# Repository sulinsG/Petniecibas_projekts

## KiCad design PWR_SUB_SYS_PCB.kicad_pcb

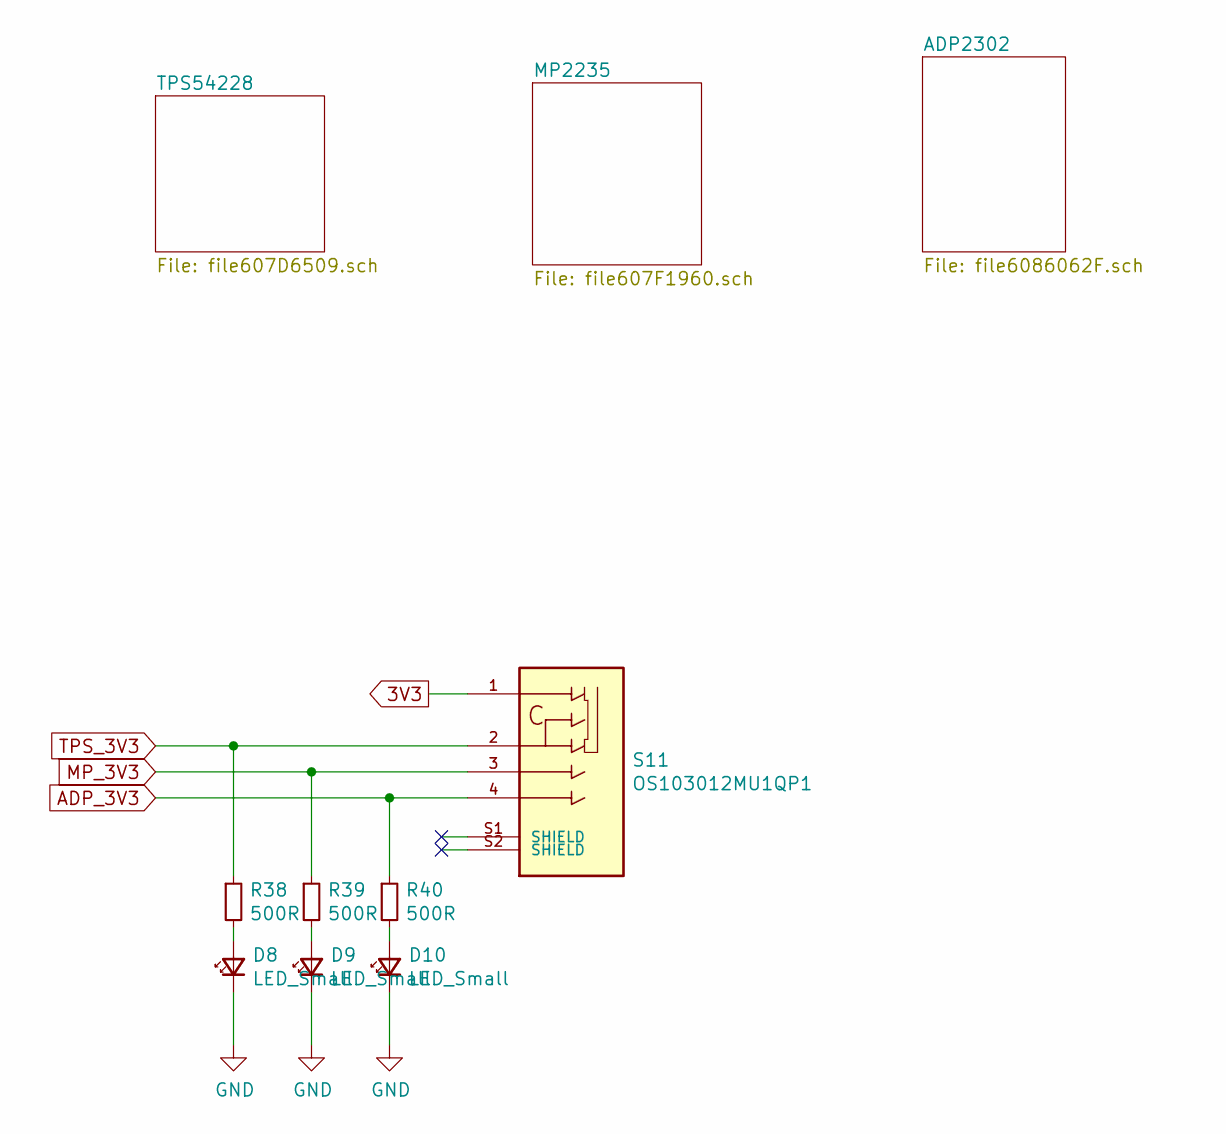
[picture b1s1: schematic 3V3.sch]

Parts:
D8, D9, D10: LED_Small; D_0603_1608Metric_Pad1.05x0.95mm_HandSolder
R38, R39, R40: 500R; R_0805_2012Metric_Pad1.20x1.40mm_HandSolder
S11: OS103012MU1QP1; SW_OS103012MU1QP1; PARTREV 8 Aug 17

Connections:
3V3: S11.1; also elsewhere on the board
ADP_3V3: R40.1, S11.4; also elsewhere on the board
GND: D8.1 (K), D9.1 (K), D10.1 (K); also elsewhere on the board
unnamed: D8.2 (A), R38.2
unnamed: D9.2 (A), R39.2
unnamed: D10.2 (A), R40.2
TPS_3V3: R38.1, S11.2; also elsewhere on the board

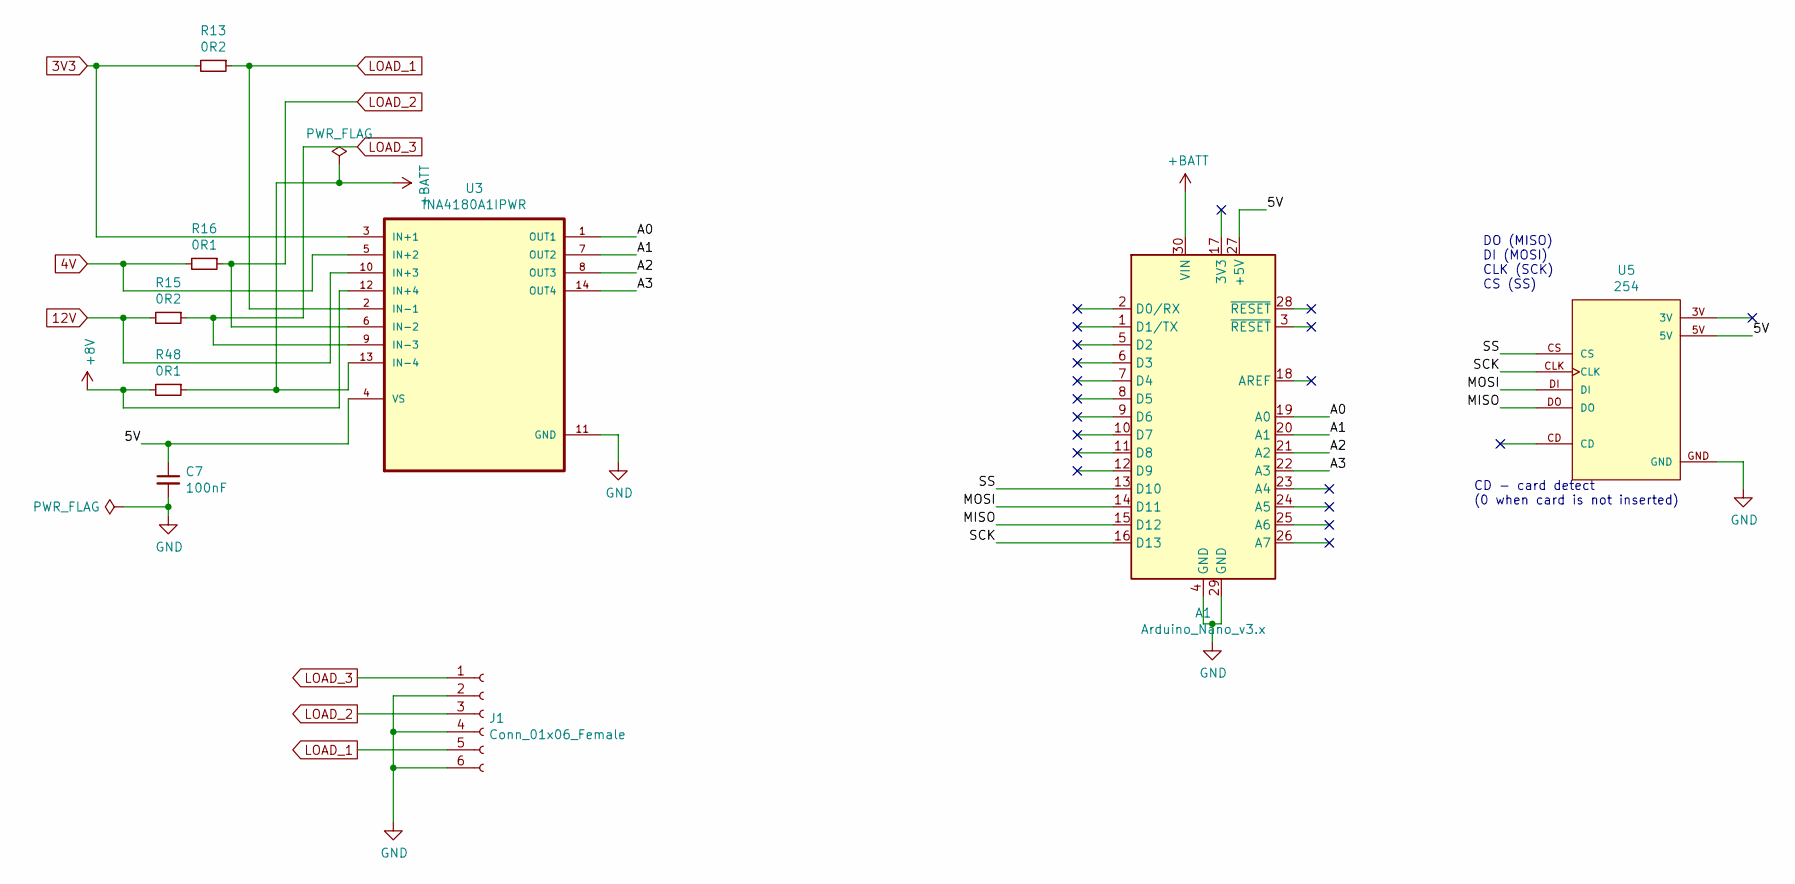
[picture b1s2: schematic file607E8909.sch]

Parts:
A1: Arduino_Nano_v3.x; Arduino_Nano
C7: 100nF; C_0603_1608Metric_Pad1.08x0.95mm_HandSolder
J1: Conn_01x06_Female; PinSocket_1x06_P2.54mm_Vertical
R13, R15: 0R2; R_0612_1632Metric_Pad1.18x3.40mm_HandSolder
R16, R48: 0R1; R_1020_2550Metric_Pad1.33x5.20mm_HandSolder
U3: INA4180A1IPWR; SOP65P640X120-14N
U5: 254; MODULE_254; PARTREV N/A

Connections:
3V3: R13.2, U3.3 (IN+1); also elsewhere on the board
4V: R16.2, U3.5 (IN+2); also elsewhere on the board
12V: R15.2, U3.10 (IN+3); also elsewhere on the board
+8V: R48.2, U3.12 (IN+4); also elsewhere on the board
+BATT: A1.30 (VIN), R48.1, U3.13 (IN-4); also elsewhere on the board
/Data logging/5V: A1.27 (+5V), C7.1, U3.4 (VS), U5.5V
/Data logging/A0: A1.19 (A0), U3.1 (OUT1)
/Data logging/A1: A1.20 (A1), U3.7 (OUT2)
/Data logging/A2: A1.21 (A2), U3.8 (OUT3)
/Data logging/A3: A1.22 (A3), U3.14 (OUT4)
/Data logging/MISO: A1.15 (D12), U5.DO
/Data logging/MOSI: A1.14 (D11), U5.DI
/Data logging/SCK: A1.16 (D13), U5.CLK
/Data logging/SS: A1.13 (D10), U5.CS
GND: A1.4 (GND), A1.29 (GND), C7.2, J1.2, J1.4, J1.6, U3.11 (GND), U5.GND; also elsewhere on the board
LOAD_1: J1.5, R13.1, U3.2 (IN-1)
LOAD_2: J1.3, R16.1, U3.6 (IN-2)
LOAD_3: J1.1, R15.1, U3.9 (IN-3)

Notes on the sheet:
DO (MISO) DI (MOSI) CLK (SCK) CS (SS)
CD - card detect (0 when card is not inserted)

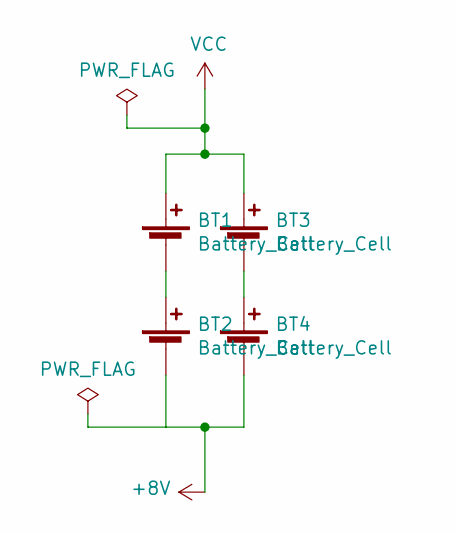
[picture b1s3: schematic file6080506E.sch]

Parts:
BT1, BT2, BT3, BT4: Battery_Cell; PinHeader_1x02_P2.54mm_Vertical

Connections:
+8V: BT2.2 (-), BT4.2 (-); also elsewhere on the board
unnamed: BT1.2 (-), BT2.1 (+)
unnamed: BT3.2 (-), BT4.1 (+)
VCC: BT1.1 (+), BT3.1 (+)

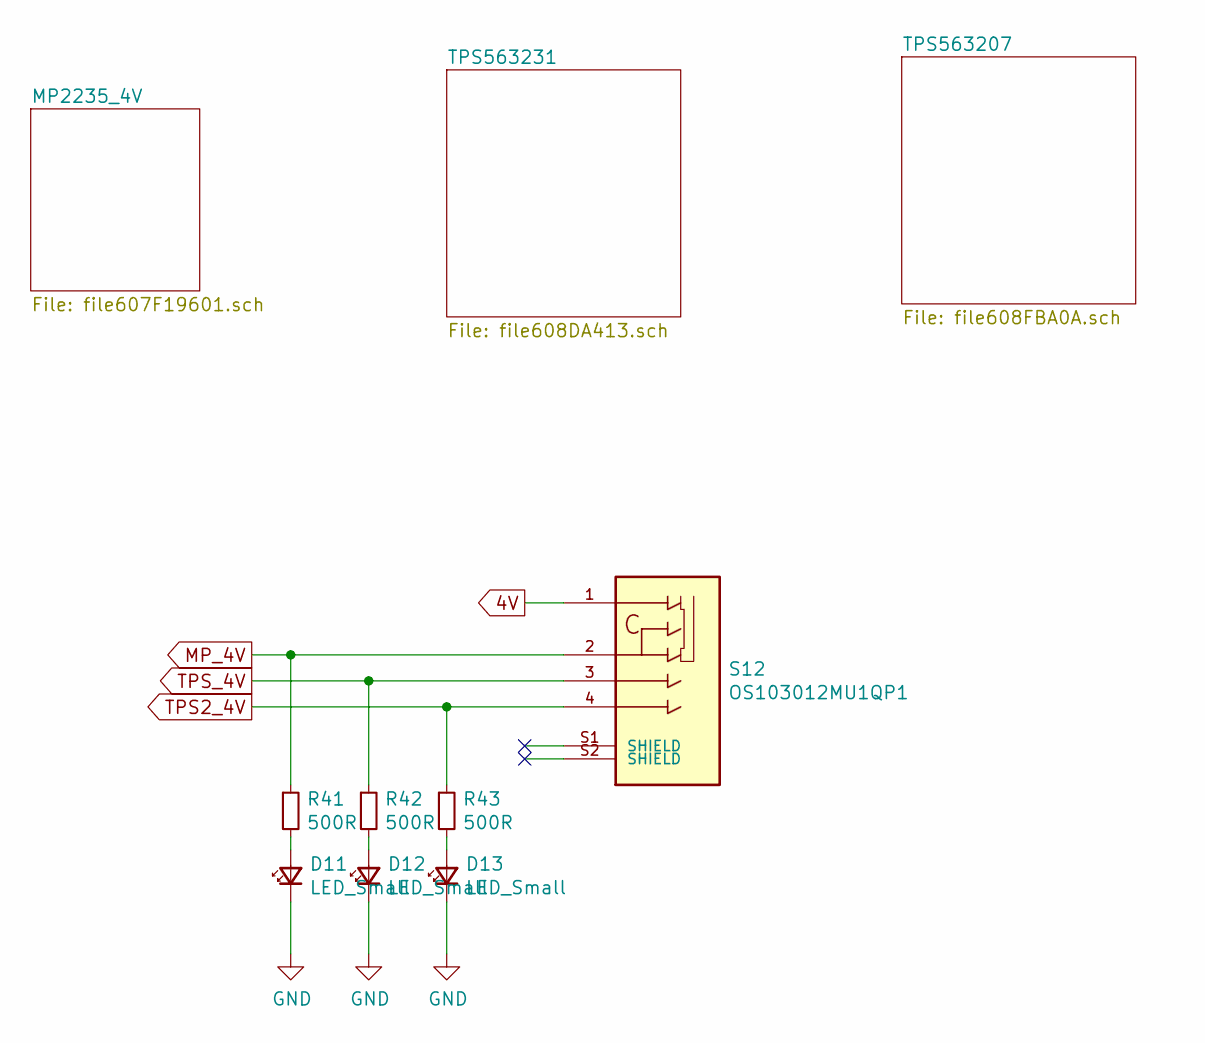
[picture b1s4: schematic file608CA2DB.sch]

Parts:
D11, D12, D13: LED_Small; D_0603_1608Metric_Pad1.05x0.95mm_HandSolder
R41, R42, R43: 500R; R_0805_2012Metric_Pad1.20x1.40mm_HandSolder
S12: OS103012MU1QP1; SW_OS103012MU1QP1; PARTREV 8 Aug 17

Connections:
4V: S12.1; also elsewhere on the board
GND: D11.1 (K), D12.1 (K), D13.1 (K); also elsewhere on the board
MP_4V: R41.1, S12.2; also elsewhere on the board
unnamed: D11.2 (A), R41.2
unnamed: D12.2 (A), R42.2
unnamed: D13.2 (A), R43.2
TPS2_4V: R43.1, S12.4; also elsewhere on the board
TPS_4V: R42.1, S12.3; also elsewhere on the board

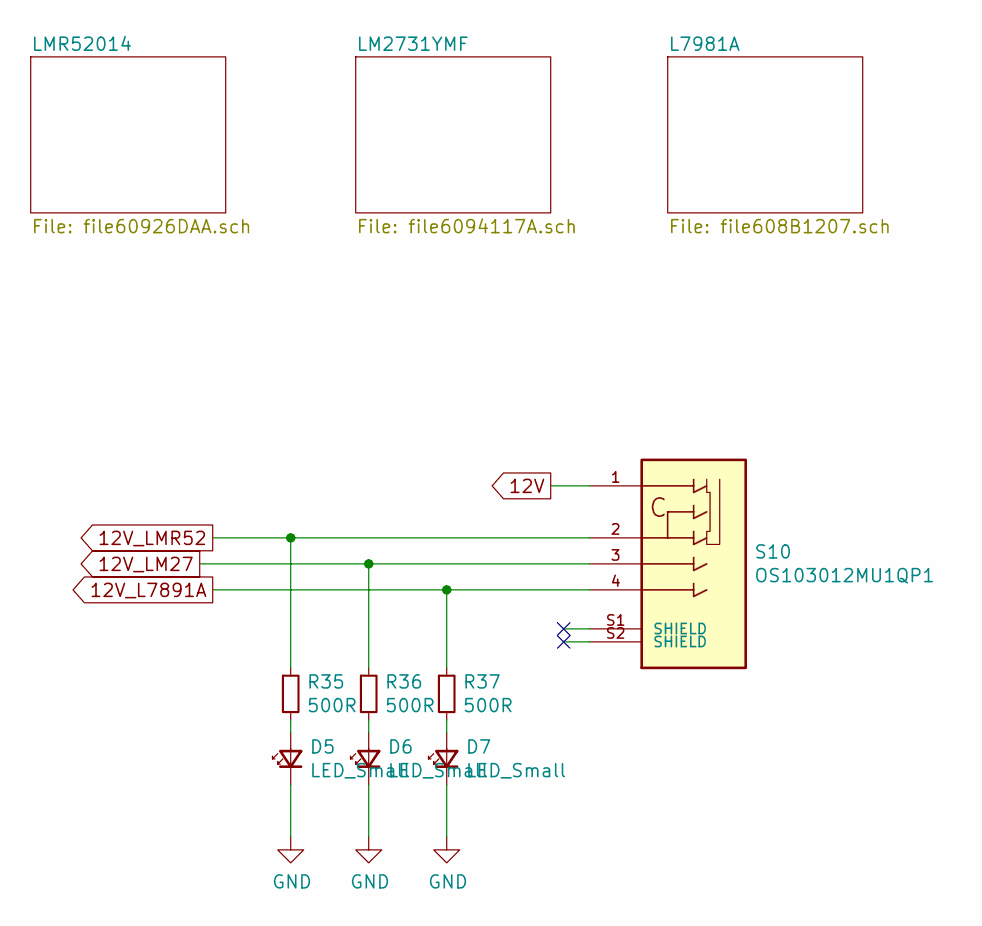
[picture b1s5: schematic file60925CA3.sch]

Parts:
D5, D6, D7: LED_Small; D_0603_1608Metric_Pad1.05x0.95mm_HandSolder
R35, R36, R37: 500R; R_0805_2012Metric_Pad1.20x1.40mm_HandSolder
S10: OS103012MU1QP1; SW_OS103012MU1QP1; PARTREV 8 Aug 17

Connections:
12V: S10.1; also elsewhere on the board
12V_L7891A: R37.1, S10.4; also elsewhere on the board
12V_LM27: R36.1, S10.3; also elsewhere on the board
12V_LMR52: R35.1, S10.2; also elsewhere on the board
GND: D5.1 (K), D6.1 (K), D7.1 (K); also elsewhere on the board
unnamed: D5.2 (A), R35.2
unnamed: D6.2 (A), R36.2
unnamed: D7.2 (A), R37.2

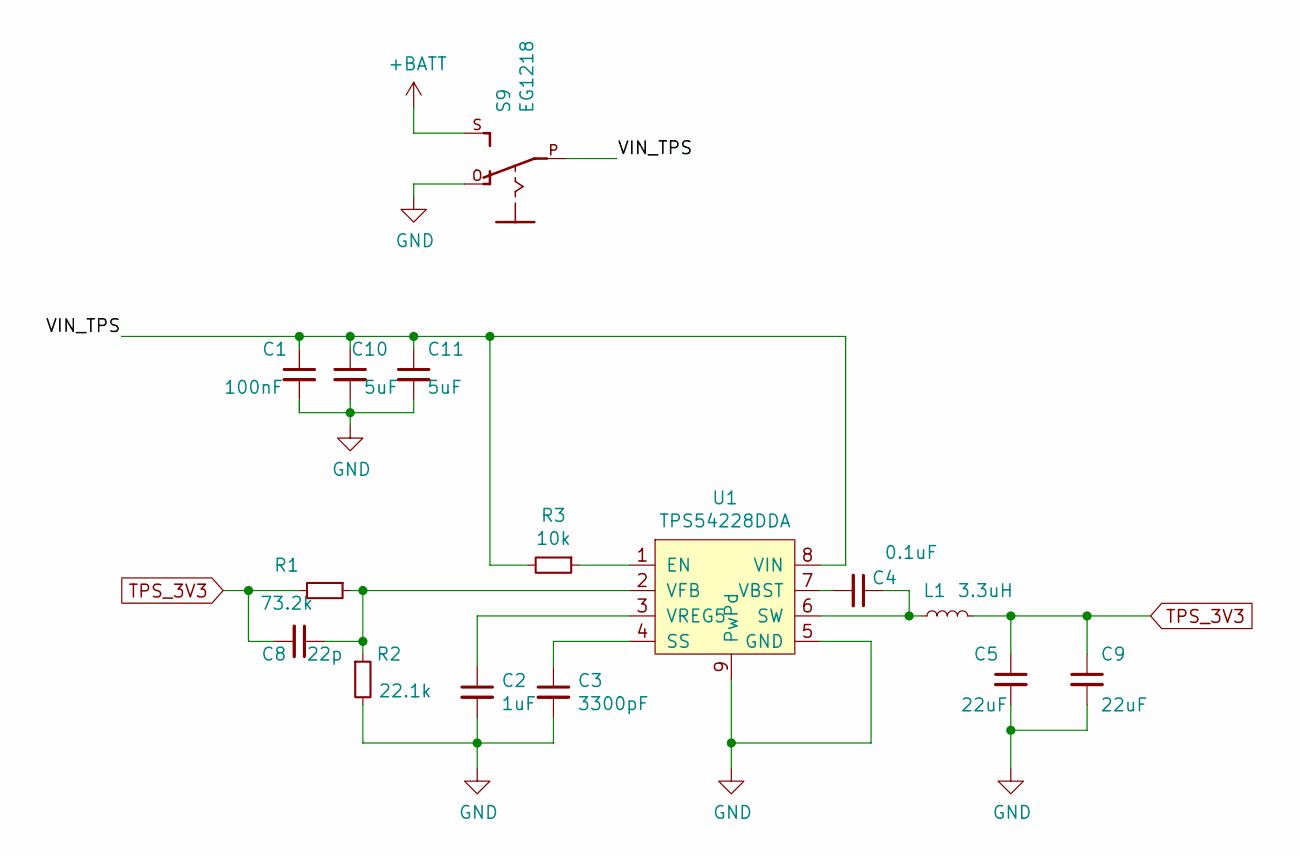
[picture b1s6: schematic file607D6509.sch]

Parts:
C1: 100nF; C_0603_1608Metric_Pad1.08x0.95mm_HandSolder
C2: 1uF; C_0603_1608Metric_Pad1.08x0.95mm_HandSolder
C3: 3300pF; C_0603_1608Metric_Pad1.08x0.95mm_HandSolder
C4: 0.1uF; C_0603_1608Metric_Pad1.08x0.95mm_HandSolder
C5, C9: 22uF; C_0805_2012Metric_Pad1.18x1.45mm_HandSolder
C8: 22p; C_0805_2012Metric_Pad1.18x1.45mm_HandSolder
C10, C11: 5uF; C_1206_3216Metric_Pad1.33x1.80mm_HandSolder
L1: 3.3uH; HM66M
R1: 73.2k; R_0805_2012Metric_Pad1.20x1.40mm_HandSolder
R2: 22.1k; R_0603_1608Metric_Pad0.98x0.95mm_HandSolder
R3: 10k; R_0805_2012Metric_Pad1.20x1.40mm_HandSolder
S9: EG1218
U1: TPS54228DDA; NOPB

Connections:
+BATT: S9.S; also elsewhere on the board
/3V3/TPS54228/VIN_TPS: C1.1, C10.1, C11.1, R3.2, S9.P, U1.8 (VIN)
GND: C1.2, C2.2, C3.2, C5.2, C9.2, C10.2, C11.2, R2.2, S9.O, U1.5 (GND), U1.9 (PwPd), U1.10, U1.11, U1.12, U1.13, U1.14, U1.15, U1.16, U1.17; also elsewhere on the board
unnamed: C2.1, U1.3 (VREG5)
unnamed: C3.1, U1.4 (SS)
unnamed: C4.1, L1.1, U1.6 (SW)
unnamed: C4.2, U1.7 (VBST)
unnamed: C8.1, R1.1, R2.1, U1.2 (VFB)
unnamed: R3.1, U1.1 (EN)
TPS_3V3: C5.1, C8.2, C9.1, L1.2, R1.2; also elsewhere on the board

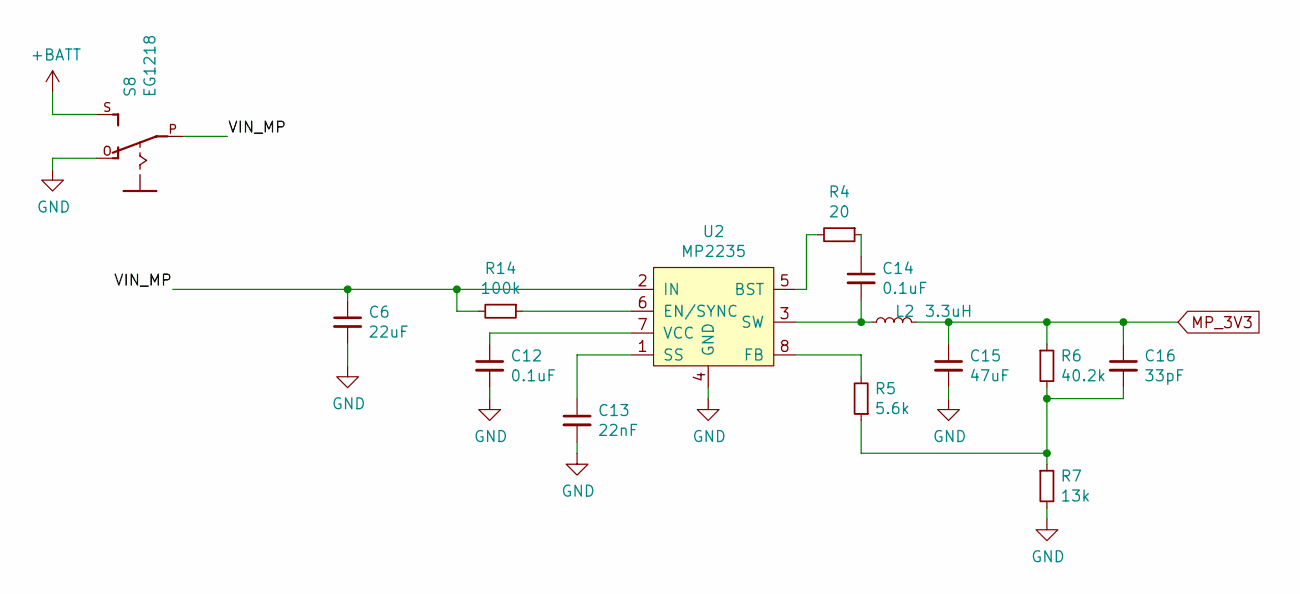
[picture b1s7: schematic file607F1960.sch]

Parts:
C6: 22uF; C_0805_2012Metric_Pad1.18x1.45mm_HandSolder
C12, C14: 0.1uF; C_0603_1608Metric_Pad1.08x0.95mm_HandSolder
C13: 22nF; C_0603_1608Metric_Pad1.08x0.95mm_HandSolder
C15: 47uF; C_1206_3216Metric_Pad1.33x1.80mm_HandSolder
C16: 33pF; C_0603_1608Metric_Pad1.08x0.95mm_HandSolder
L2: 3.3uH; HM66M
R4: 20; R_0603_1608Metric_Pad0.98x0.95mm_HandSolder
R5: 5.6k; R_0805_2012Metric_Pad1.20x1.40mm_HandSolder
R6: 40.2k; R_0805_2012Metric_Pad1.20x1.40mm_HandSolder
R7: 13k; R_0805_2012Metric_Pad1.20x1.40mm_HandSolder
R14: 100k; R_0805_2012Metric_Pad1.20x1.40mm_HandSolder
S8: EG1218
U2: MP2235; SOT65P280X100-8N

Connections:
+BATT: S8.S; also elsewhere on the board
GND: C6.2, C12.2, C13.2, C15.2, R7.2, S8.O, U2.4 (GND); also elsewhere on the board
unnamed: C12.1, U2.7 (VCC)
unnamed: C13.1, U2.1 (SS)
unnamed: C14.1, R4.1
unnamed: C14.2, L2.1, U2.3 (SW)
unnamed: C16.2, R5.1, R6.2, R7.1
unnamed: R4.2, U2.5 (BST)
unnamed: R5.2, U2.8 (FB)
unnamed: R14.1, U2.6 (EN/SYNC)

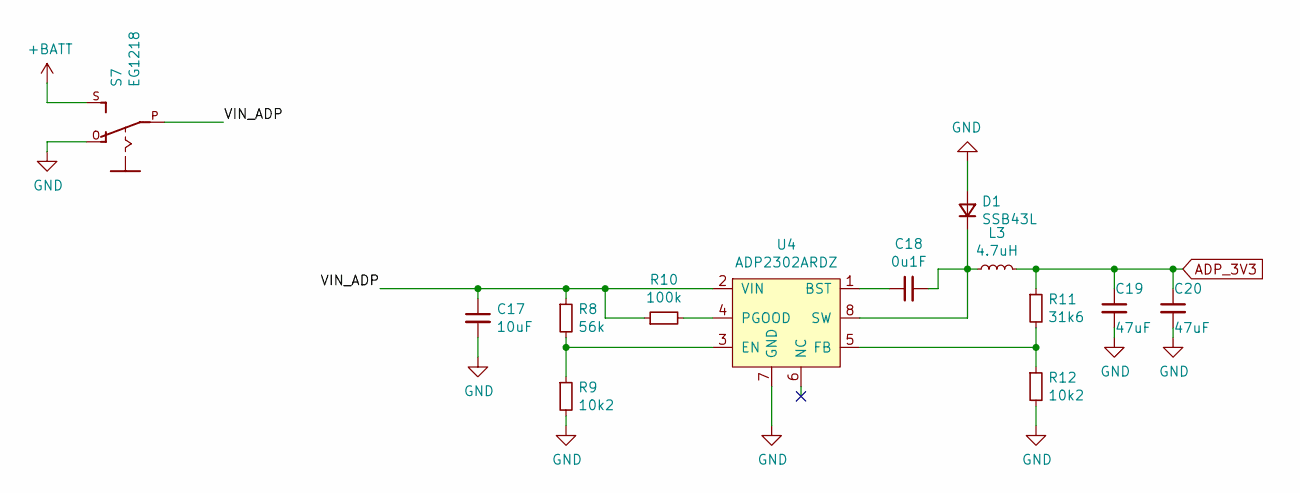
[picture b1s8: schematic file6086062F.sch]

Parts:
C17: 10uF; C_0805_2012Metric_Pad1.18x1.45mm_HandSolder
C18: 0u1F; C_0603_1608Metric_Pad1.08x0.95mm_HandSolder
C19, C20: 47uF; C_1206_3216Metric_Pad1.33x1.80mm_HandSolder
D1: SSB43L; D_SOD-123
L3: 4.7uH; IND_1255AY-4R7M=P3
R8: 56k; R_0805_2012Metric_Pad1.20x1.40mm_HandSolder
R9, R12: 10k2; R_0805_2012Metric_Pad1.20x1.40mm_HandSolder
R10: 100k; R_0805_2012Metric_Pad1.20x1.40mm_HandSolder
R11: 31k6; R_0805_2012Metric_Pad1.20x1.40mm_HandSolder
S7: EG1218
U4: ADP2302ARDZ; SOIC127P600X175-9N

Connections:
+BATT: S7.S; also elsewhere on the board
/3V3/ADP2302/VIN_ADP: C17.1, R8.1, R10.1, S7.P, U4.2 (VIN)
ADP_3V3: C19.1, C20.1, L3.2, R11.1; also elsewhere on the board
GND: C17.2, C19.2, C20.2, D1.2 (A), R9.2, R12.2, S7.O, U4.7 (GND); also elsewhere on the board
unnamed: C18.1, U4.1 (BST)
unnamed: C18.2, D1.1 (K), L3.1, U4.8 (SW)
unnamed: R8.2, R9.1, U4.3 (EN)
unnamed: R10.2, U4.4 (PGOOD)
unnamed: R11.2, R12.1, U4.5 (FB)

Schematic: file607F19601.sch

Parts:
C6: 22uF; C_0805_2012Metric_Pad1.18x1.45mm_HandSolder
C12, C14: 0.1uF; C_0603_1608Metric_Pad1.08x0.95mm_HandSolder
C13: 22nF; C_0603_1608Metric_Pad1.08x0.95mm_HandSolder
C15: 47uF; C_1206_3216Metric_Pad1.33x1.80mm_HandSolder
C16: 33pF; C_0603_1608Metric_Pad1.08x0.95mm_HandSolder
L2: 3.3uH; HM66M
R4: 20; R_0603_1608Metric_Pad0.98x0.95mm_HandSolder
R5: 3k; R_0805_2012Metric_Pad1.20x1.40mm_HandSolder
R6: 40.2k; R_0805_2012Metric_Pad1.20x1.40mm_HandSolder
R7: 10.2k; R_0805_2012Metric_Pad1.20x1.40mm_HandSolder
R14: 19k; R_0805_2012Metric_Pad1.20x1.40mm_HandSolder
S6: EG1218
U2: MP2235; SOT65P280X100-8N

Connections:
+BATT: S6.S; also elsewhere on the board
GND: C6.2, C12.2, C13.2, C15.2, R7.2, S6.O, U2.4 (GND); also elsewhere on the board
unnamed: C12.1, U2.7 (VCC)
unnamed: C13.1, U2.1 (SS)
unnamed: C14.1, R4.1
unnamed: C14.2, L2.1, U2.3 (SW)
unnamed: C16.2, R5.1, R6.2, R7.1
unnamed: R4.2, U2.5 (BST)
unnamed: R5.2, U2.8 (FB)
unnamed: R14.1, U2.6 (EN/SYNC)

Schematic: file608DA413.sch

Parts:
C27: 10uF; C_0805_2012Metric_Pad1.18x1.45mm_HandSolder
C28: 100nF; C_0603_1608Metric_Pad1.08x0.95mm_HandSolder
C29, C30, C31: 47uF; C_1206_3216Metric_Pad1.33x1.80mm_HandSolder
L5: 4.7uH; IND_1255AY-4R7M=P3
R22: 56k; R_0603_1608Metric_Pad0.98x0.95mm_HandSolder
R23: 10k; R_0805_2012Metric_Pad1.20x1.40mm_HandSolder
R44: 700R; R_0603_1608Metric_Pad0.98x0.95mm_HandSolder
S5: EG1218
U7: TPS563231DRLR; SOT50P160X60-6N

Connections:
+BATT: S5.S; also elsewhere on the board
/4V/TPS563231/VIN_TPS: C27.1, S5.P, U7.1 (VIN), U7.5 (EN)
GND: C27.2, C29.2, C30.2, C31.2, R23.2, S5.O, U7.3 (GND); also elsewhere on the board
unnamed: C28.1, L5.1, U7.2 (SW)
unnamed: C28.2, U7.4 (BST)
unnamed: R22.2, R44.1
unnamed: R44.2, U7.6 (FB)
TPS_4V: C29.1, C30.1, C31.1, L5.2, R22.1, R23.1; also elsewhere on the board

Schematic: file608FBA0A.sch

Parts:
C32, C34: 10uF; C_0805_2012Metric_Pad1.18x1.45mm_HandSolder
C33, C36: 22 uF; C_0805_2012Metric_Pad1.18x1.45mm_HandSolder
C35: 0.1uF; C_0603_1608Metric_Pad1.08x0.95mm_HandSolder
C37: 100nF; C_0603_1608Metric_Pad1.08x0.95mm_HandSolder
L6: 4.7uH; IND_1255AY-4R7M=P3
R24, R25: 10k; R_0805_2012Metric_Pad1.20x1.40mm_HandSolder
R26: 39k; R_0805_2012Metric_Pad1.20x1.40mm_HandSolder
R45: 700R; R_0603_1608Metric_Pad0.98x0.95mm_HandSolder
S4: EG1218
U8: TPS563207DRLR; SOT-563

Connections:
+BATT: S4.S; also elsewhere on the board
/4V/TPS563207/VIN_TPS: C32.1, C34.1, C35.1, R24.2, S4.P, U8.1 (VIN)
GND: C32.2, C33.2, C34.2, C35.2, C36.2, R25.2, S4.O, U8.3 (GND); also elsewhere on the board
unnamed: C37.1, U8.4 (BST)
unnamed: C37.2, L6.2, U8.2 (SW)
unnamed: R24.1, U8.5 (EN)
unnamed: R25.1, R26.1, U8.6 (FB)
unnamed: R26.2, R45.1
TPS2_4V: C33.1, C36.1, L6.1, R45.2; also elsewhere on the board

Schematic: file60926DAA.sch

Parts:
C38: 2.2uF; C_0805_2012Metric_Pad1.18x1.45mm_HandSolder
C39: 220pF; C_0603_1608Metric_Pad1.08x0.95mm_HandSolder
C40: 4.7uF; C_1206_3216Metric_Pad1.33x1.80mm_HandSolder
D2: D_Schottky; D_SOD-123
L7: 10uH; SDE1006A-100M
R28: 13.3k; R_0805_2012Metric_Pad1.20x1.40mm_HandSolder
R29: 115k; R_0805_2012Metric_Pad1.20x1.40mm_HandSolder
R46: 2k; R_0805_2012Metric_Pad1.20x1.40mm_HandSolder
S3: EG1218
U9: LMR62014XMFE_NOPB; SOT95P280X145-5N; PARTREV B

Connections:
12V_LMR52: C39.1, C40.1, D2.1 (K), R46.1; also elsewhere on the board
+BATT: S3.S; also elsewhere on the board
/12V/LMR52014/VIN_LMR: C38.1, L7.1, S3.P, U9.4 (~SHDN), U9.5 (VIN)
GND: C38.2, C40.2, R28.2, S3.O, U9.2 (GND); also elsewhere on the board
unnamed: C39.2, R28.1, R29.2, U9.3 (FB)
unnamed: D2.2 (A), L7.2, U9.1 (SW)
unnamed: R29.1, R46.2

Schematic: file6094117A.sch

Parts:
C41: 2.2uF; C_0805_2012Metric_Pad1.18x1.45mm_HandSolder
C43: 220pF; C_0603_1608Metric_Pad1.08x0.95mm_HandSolder
C44: 4.7uF; C_1206_3216Metric_Pad1.33x1.80mm_HandSolder
D3: D_Schottky; D_SOD-123
L8: 10uH; SDE1006A-100M
R27: 115k; R_0805_2012Metric_Pad1.20x1.40mm_HandSolder
R30: 13.3k; R_0805_2012Metric_Pad1.20x1.40mm_HandSolder
R47: 2k; R_0805_2012Metric_Pad1.20x1.40mm_HandSolder
S2: EG1218
U10: LM2731YMF; SOT95P280X145-5N

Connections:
12V_LM27: C43.2, C44.1, D3.1 (K), R27.2; also elsewhere on the board
+BATT: S2.S; also elsewhere on the board
/12V/LM2731YMF/VIN_LMR: C41.1, L8.1, S2.P, U10.4 (~SD), U10.5 (VIN)
GND: C41.2, C44.2, R30.2, S2.O, U10.2 (GND); also elsewhere on the board
unnamed: C43.1, R30.1, R47.1, U10.3 (FB)
unnamed: D3.2 (A), L8.2, U10.1 (SW)
unnamed: R27.1, R47.2

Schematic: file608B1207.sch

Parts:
C50: 22uF; C_1210_3225Metric_Pad1.33x2.70mm_HandSolder
C51: 1uF; C_0805_2012Metric_Pad1.18x1.45mm_HandSolder
C52: 680p; C_0603_1608Metric_Pad1.08x0.95mm_HandSolder
C53: 390nF; C_0603_1608Metric_Pad1.08x0.95mm_HandSolder
C54: 4.7nF; C_0805_2012Metric
C55, C56, C57: 47uF; CP_Radial_D5.0mm_P2.00mm
D14, D15: STPS1L20M
L10: 27 uH; 744770127
Q1: STN4NF03L
R31: 1k; R_0805_2012Metric_Pad1.20x1.40mm_HandSolder
R50: 1k8; R_0805_2012Metric_Pad1.20x1.40mm_HandSolder
R51: 2k2; R_0805_2012Metric_Pad1.20x1.40mm_HandSolder
R52: 82k; R_0805_2012Metric_Pad1.20x1.40mm_HandSolder
R53: 4k32; R_0805_2012Metric_Pad1.20x1.40mm_HandSolder
S13: EG1218
U12: L7981A-Regulator_Switching; L7981A

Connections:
12V_L7891A: C54.1, C55.1, C56.1, C57.1, D15.1 (K), R52.1; also elsewhere on the board
+BATT: S13.S; also elsewhere on the board
/12V/L7981A/VIN_L798: C50.1, C51.1, R31.2, S13.P, U12.8 (VCC)
GND: C50.2, C51.2, C55.2, C56.2, C57.2, D14.2 (A), Q1.3 (S), R53.2, S13.O, U12.7 (GND); also elsewhere on the board
unnamed: C52.1, R50.1, R51.2, R52.2, R53.1, U12.5 (FB)
unnamed: C52.2, C53.2, U12.4 (COMP)
unnamed: C53.1, R50.2
unnamed: C54.2, R51.1
unnamed: D14.1 (K), L10.1, Q1.1 (G), U12.1 (OUT)
unnamed: D15.2 (A), L10.2, Q1.2 (D)
unnamed: R31.1, U12.3 (EN)

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
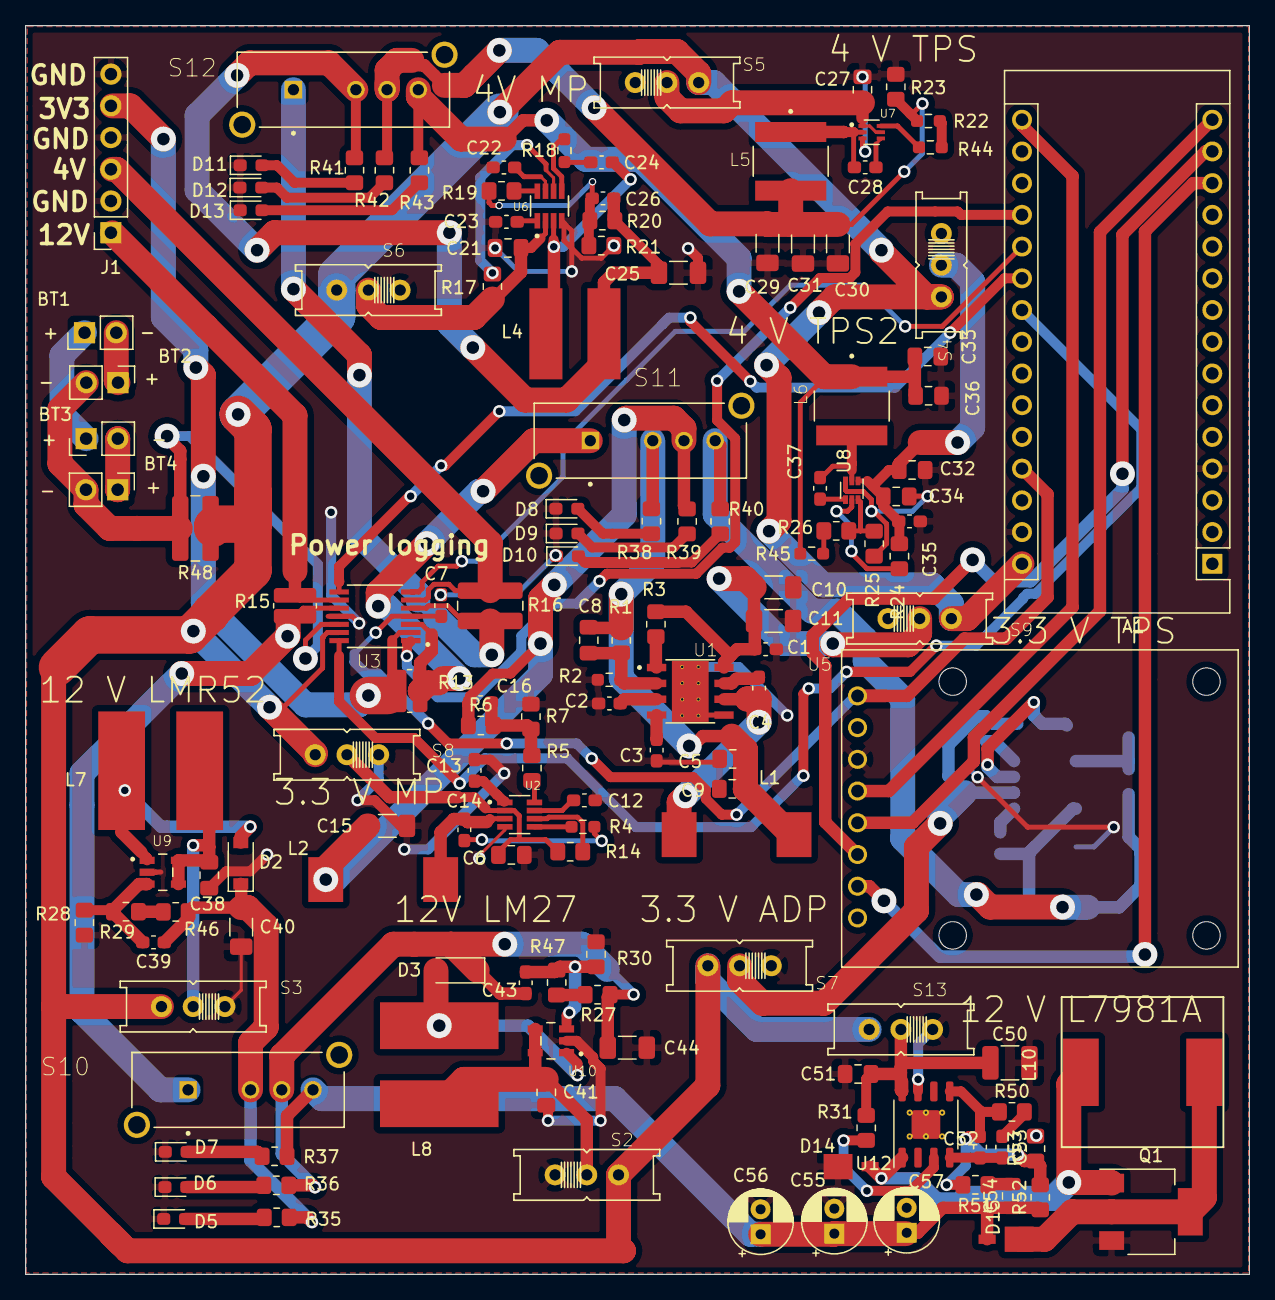
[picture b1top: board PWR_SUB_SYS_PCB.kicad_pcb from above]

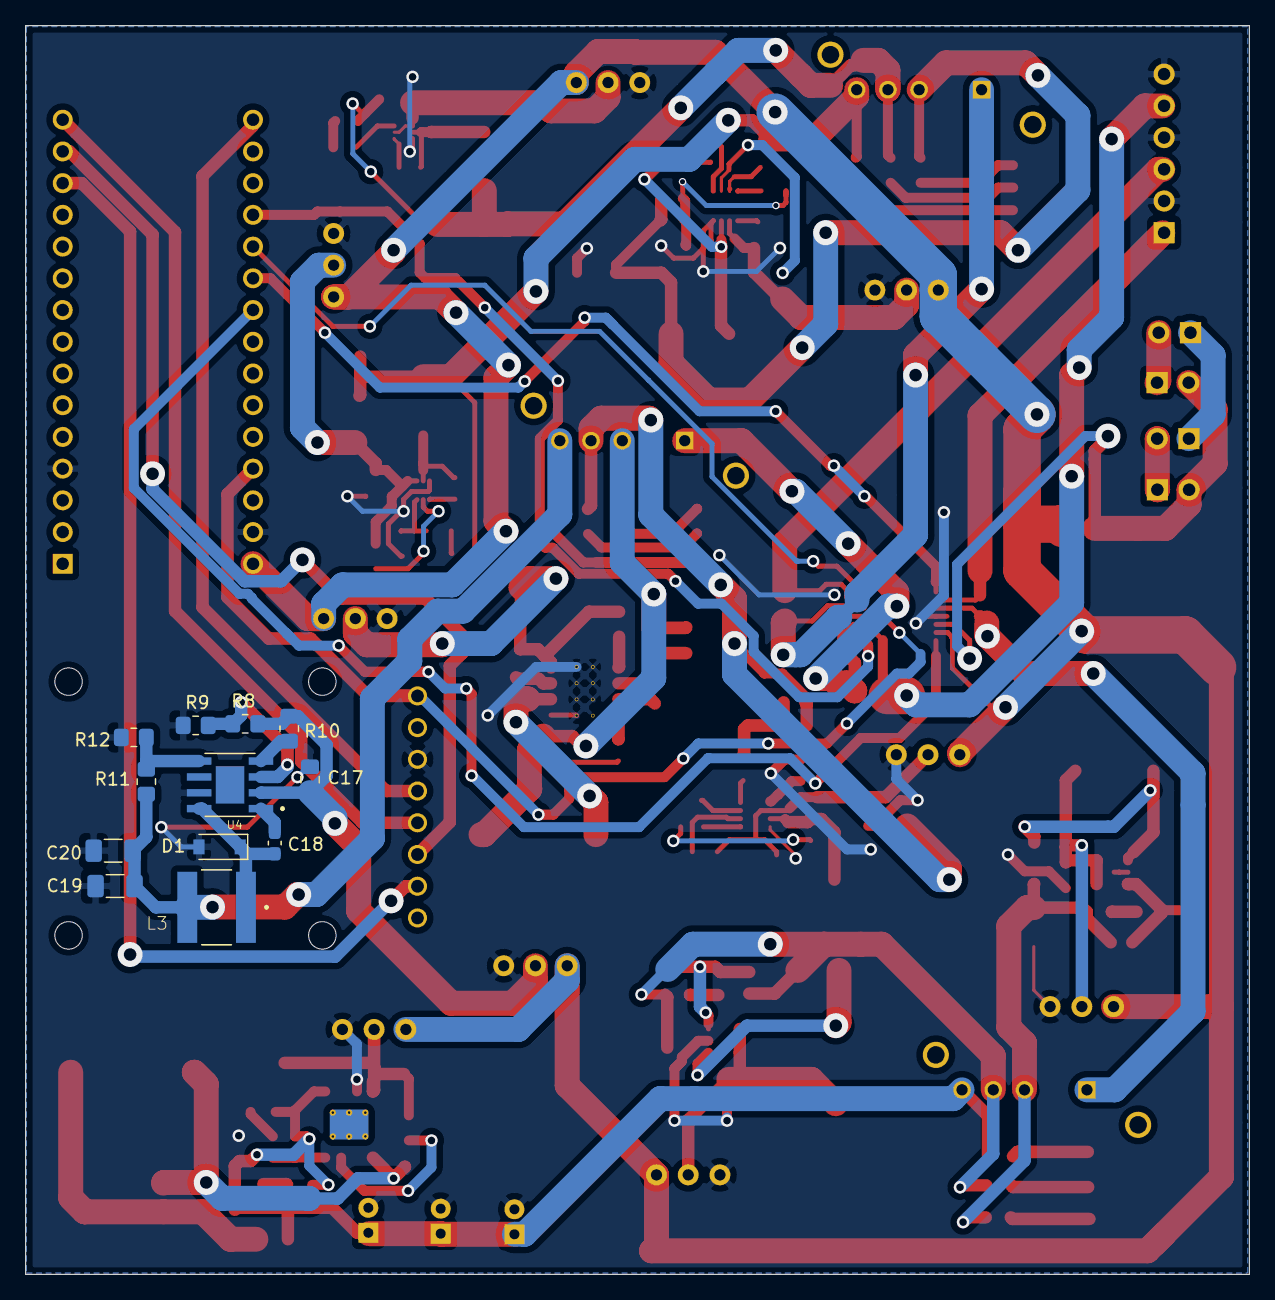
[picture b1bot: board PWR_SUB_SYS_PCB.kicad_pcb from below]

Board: 2 copper layers, 98.0 x 100.0 mm, 153 parts (12 on the bottom side), 97 nets.

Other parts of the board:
C21: 22uF; C_0805_2012Metric_Pad1.18x1.45mm_HandSolder
C22, C24: 0.1uF; C_0603_1608Metric_Pad1.08x0.95mm_HandSolder
C23: 22nF; C_0603_1608Metric_Pad1.08x0.95mm_HandSolder
C25: 47uF; C_1206_3216Metric_Pad1.33x1.80mm_HandSolder
C26: 33pF; C_0603_1608Metric_Pad1.08x0.95mm_HandSolder
L4: 3.3uH; HM66M
R17: 19k; R_0805_2012Metric_Pad1.20x1.40mm_HandSolder
R18: 20; R_0603_1608Metric_Pad0.98x0.95mm_HandSolder
R19: 3k; R_0805_2012Metric_Pad1.20x1.40mm_HandSolder
R20: 40.2k; R_0805_2012Metric_Pad1.20x1.40mm_HandSolder
R21: 10.2k; R_0805_2012Metric_Pad1.20x1.40mm_HandSolder
U6: MP2235; SOT65P280X100-8N

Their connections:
GND: C21.2, C22.2, C23.2, C25.2, R21.2, U6.4; also elsewhere on the board
MP_4V: C25.1, C26.1, L4.2, R20.1; also elsewhere on the board
unnamed: C22.1, U6.7
unnamed: C23.1, U6.1
unnamed: C24.1, R18.1
unnamed: C24.2, L4.1, U6.3
unnamed: C26.2, R19.1, R20.2, R21.1
unnamed: R17.1, U6.6
unnamed: R18.2, U6.5
unnamed: R19.2, U6.8

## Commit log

2021-04-19 Added first version of 3V3 Buck voltage regulator
2021-04-19 testing git
2021-04-20 added data logging
2021-04-22 full schematic, version 1.0
2021-04-22 removed extra stuff
2021-04-28 component layout complete
2021-04-28 incomplete pcb
2021-04-28 finished pcb v1
2021-04-29 test
2021-04-29 second test
2021-04-29 fixed the unlinked hierachies
2021-05-10 changed unavailable parts, added overall consumed current measuring
2021-05-10 finished pcb v2
2021-05-10 tests
2021-05-10 tests2
